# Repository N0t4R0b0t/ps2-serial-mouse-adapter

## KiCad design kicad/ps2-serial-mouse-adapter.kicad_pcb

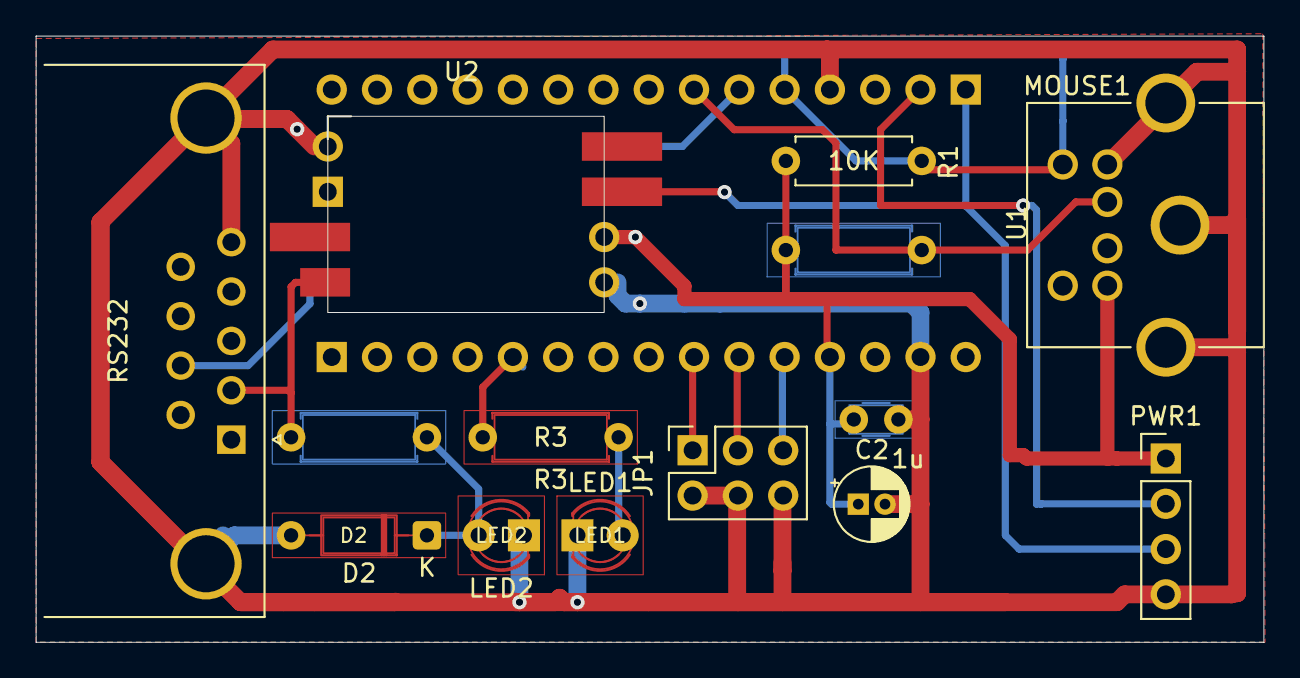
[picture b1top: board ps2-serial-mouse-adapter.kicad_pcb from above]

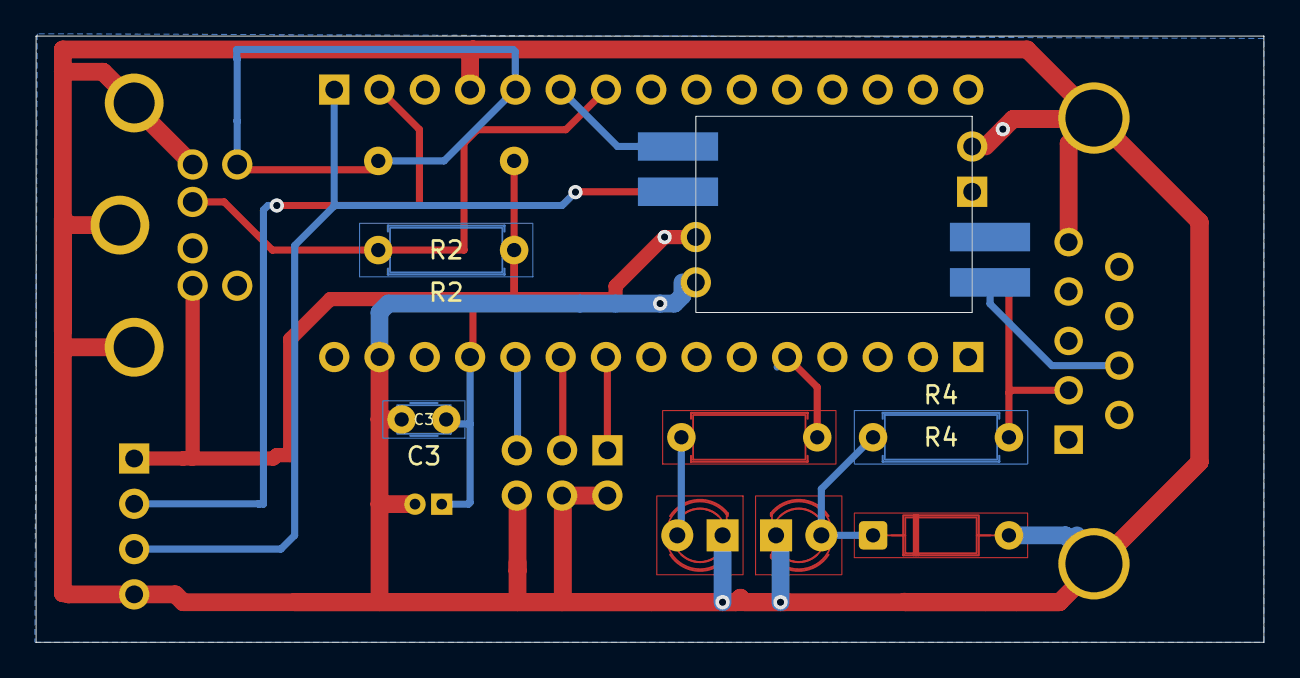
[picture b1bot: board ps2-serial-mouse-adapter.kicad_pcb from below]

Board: 2 copper layers, 68.9 x 34.0 mm, 15 parts (3 on the bottom side), 14 nets.

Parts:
C2: 1u; CP_Radial_D4.0mm_P1.50mm
C3: 100nF; C_Disc_D3.0mm_W1.6mm_P2.50mm
D2: 1N4148; D_DO-35_SOD27_P7.62mm_Horizontal
JP1: Conn_02x03_Odd_Even; PinSocket_2x03_P2.54mm_Vertical
LED1, LED2: LED; LED_D3.0mm
MOUSE1: Mini-DIN-6; Mini_DIN_6_LCSC_C77848
PWR1: Conn_Panel_1x04; PinHeader_1x04_P2.54mm_Vertical
R1, R2: 10K; R_Axial_DIN0207_L6.3mm_D2.5mm_P7.62mm_Horizontal
R3: 330; R_Axial_DIN0207_L6.3mm_D2.5mm_P7.62mm_Horizontal
R4: 2.2k; R_Axial_DIN0207_L6.3mm_D2.5mm_P7.62mm_Horizontal
RS232: DB9_Female; DSUB-9_Female_Horizontal_P2.77x2.84mm_EdgePinOffset7.70mm_H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
U1: Arduino_Nano; Arduino_Nano_Socket
U2: MAX3232_HW027

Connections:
CLK: MOUSE1.5, R1.2, U1.5 (D2)
DATA: MOUSE1.1, R2.2, U1.7 (D4)
GND: C2.2, C3.2, D2.2 (A), JP1.2, JP1.4, LED1.1 (K), LED2.1 (K), MOUSE1.3, MOUSE1.7, PWR1.4 (GND), RS232.0 (PAD), RS232.5, U1.4 (GND), U1.29 (GND), U2.2 (GND), U2.4 (GND2)
JP12: JP1.1, U1.26 (A7)
JP34: JP1.3, U1.25 (A6)
unnamed: D2.1 (K), LED2.2 (A), R4.1
unnamed: LED1.2 (A), R3.1
unnamed: R3.2, U1.20 (A1)
unnamed: RS232.7, U2.7 (RS232_RXD2)
unnamed: R4.2, RS232.2, U2.6 (RS232_TXD1)
RTS: U1.6 (D3), U2.12 (TTL_RXD2)
RX: PWR1.2 (RX), U1.2 (D0/RX)
TX: PWR1.3 (TX), U1.1 (D1/TX), U2.10 (TTL_RXD1)
VBUS: C2.1, C3.1, MOUSE1.4, PWR1.1 (VBUS), R1.1, R2.1, U1.27 (5V), U2.1 (VCC), U2.3 (VCC2)

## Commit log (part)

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2026-05-08 Add schematic changes for MAX3232 module and Arduino Nano integration
2026-05-09 Add footprints for Arduino Nano socket and MAX3232 HW-027 module
    - Created a new footprint for the Arduino Nano socket with 2x15 pin configuration, including through-hole pads and silk screen details.
    - Added a footprint for the MAX3232 HW-027 module featuring castellated pads, through-hole and SMD pads, along with necessary fabrication outlines.
2026-05-16 Update Arduino Nano Socket footprint and adjust active layer in project file
    - Changed the active layer in the project file from 2 to 0 for better visibility.
    - Updated the Arduino Nano Socket footprint to a new version with enhanced properties and formatting.
    - Added detailed properties for reference, value, datasheet, and description with UUIDs.
    - Expanded pad definitions to include all 30 pins with consistent attributes and UUIDs.
    - Improved the footprint's rectangle yard dimensions and ensured proper layer assignments.
